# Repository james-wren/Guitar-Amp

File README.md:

# Guitar-Amp
## Description
A 4 inch and electric guitar amplifier using the LM386n-4 and J201 JFETS. Operates using 4 main stages:
1. JFET input boost, the signal coming from a guitar is very weak, so it needs to be boosted to a usable level
2. Tone control, uses a 50k POT to control the guitars tone, this stage decreases the signal strength
3. JFET tone boost, boosts the signal strength back up to usable level.
4. Audio amplification, uses the LM386n-4 to amplify the audio to ~1w, ideal for a 4 inch speaker

The board is designed to use only THT components to save money as it can ban easily soldered with basic tools, to aid in the easy assembly parts are also spread out over a almost 200mm width. Components start on the left with the 1/4 inch jack input, wrap around the top, and end on the right with the speaker output. It is mounted to the case using m2 screws.

The case is pretty simple, just a speaker on the front with the three potentiometers and input jack up top, the 12v barrel is located on the back of the case near the bottom, the case is printed in two parts, the back plate is printed seperatly and screwed on with two M2 screws.

Inside mounting holes of back plate:  

## Instructions
### Build 
1. Solder components onto the pcb, simply solder the through hole components, no special gear is needed.
2. Wire potentiometers, the input jack, 12v barrel, and the speaker. Solder using 22AWG wire to thier respective pads
3. Print case in any orientation prefered, note that supports will be needed for the main body.
4. Screw in components, the pcb and backplate use m2 screws, and the speaker uses m8.

### Usage
1. Plug in guitar, reccomend starting with this to avoid a loud, high piched noise.
2. Plug in 12v barrel to turn on amp
3. Adjust knobs to prefered tune
4. Play your guitar!

## Why I made this
Pretty simple, I don't have an AMP, but I do have a guitar (I actually built it myself). After building I decieded that I wanted to learn to play, until this I had been plugging it into my old ipod and using garage band as an amp, but this was pretty terrible so I decieded this would be a fun first hardware project

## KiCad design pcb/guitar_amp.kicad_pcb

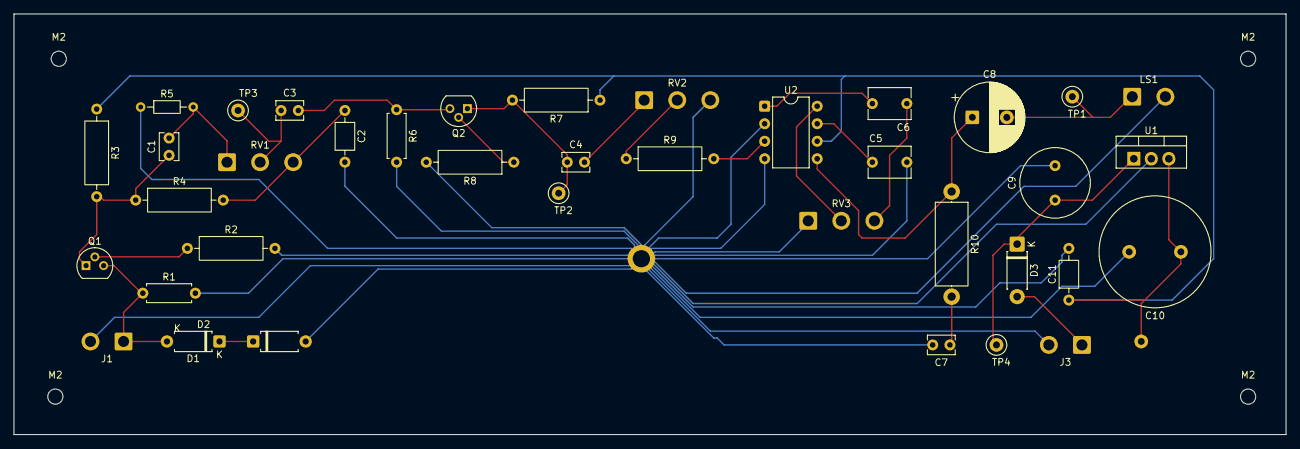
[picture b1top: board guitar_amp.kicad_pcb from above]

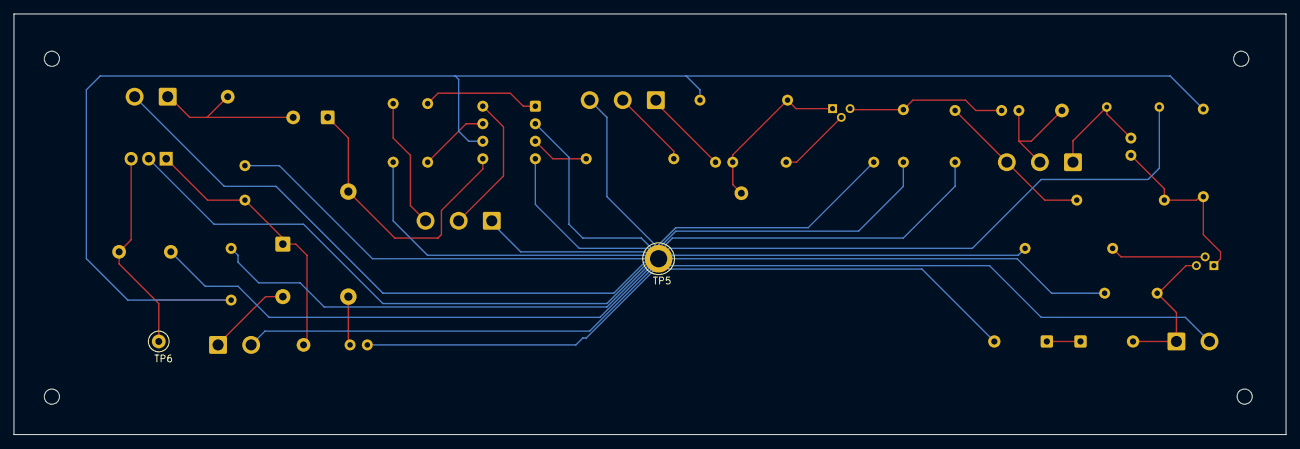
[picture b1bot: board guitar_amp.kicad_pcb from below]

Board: 2 copper layers, 184.5 x 61.0 mm, 44 parts (2 on the bottom side), 24 nets.

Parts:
C1: 6.8N; C_Disc_D3.8mm_W2.6mm_P2.50mm
C2: 10n; C_Axial_L3.8mm_D2.6mm_P7.50mm_Horizontal
C3, C4, C7: 47n; C_Disc_D3.8mm_W2.6mm_P2.50mm
C5, C6: 10uF; C_Disc_D6.0mm_W4.4mm_P5.00mm
C8: 220uF; CP_Radial_D10.0mm_P5.00mm
C9: 100uF; C_Radial_D10.0mm_H16.0mm_P5.00mm
C10: 470uF; C_Radial_D16.0mm_H31.5mm_P7.50mm
C11: 100nF; C_Axial_L3.8mm_D2.6mm_P7.50mm_Horizontal
D1, D2: 5.1v; D_A-405_P7.62mm_Horizontal
D3: 1N4007; D_DO-41_SOD81_P7.62mm_Horizontal
J1: 6.35mm Mono Jack; SolderWire-0.75sqmm_1x02_P4.8mm_D1.25mm_OD2.3mm
J3: Conn_Coaxial; SolderWire-0.75sqmm_1x02_P4.8mm_D1.25mm_OD2.3mm
LS1: 5 inch speaker; SolderWire-0.75sqmm_1x02_P4.8mm_D1.25mm_OD2.3mm
M2, M2#2, M2#3, M2#4: MountingHole_2.2mm_M2
Q1, Q2: J201; TO-92
R1, R6: 1M; R_Axial_DIN0207_L6.3mm_D2.5mm_P7.62mm_Horizontal
R2, R8: 2K2; R_Axial_DIN0309_L9.0mm_D3.2mm_P12.70mm_Horizontal
R3, R7, R9: 6K8; R_Axial_DIN0309_L9.0mm_D3.2mm_P12.70mm_Horizontal
R4: 47K; R_Axial_DIN0309_L9.0mm_D3.2mm_P12.70mm_Horizontal
R5: 22K; R_Axial_DIN0204_L3.6mm_D1.6mm_P7.62mm_Horizontal
R10: 10R; R_Axial_DIN0414_L11.9mm_D4.5mm_P15.24mm_Horizontal
RV1, RV3: 50K; SolderWire-0.75sqmm_1x03_P4.8mm_D1.25mm_OD2.3mm
RV2: A50K; SolderWire-0.75sqmm_1x03_P4.8mm_D1.25mm_OD2.3mm
TP1: Speaker; TestPoint_Loop_D2.50mm_Drill1.0mm
TP2: Boost; TestPoint_Loop_D2.50mm_Drill1.0mm
TP3: Tone; TestPoint_Loop_D2.50mm_Drill1.0mm
TP4: 12v Raw; TestPoint_Loop_D2.50mm_Drill1.0mm
TP5: GND Ref; TestPoint_Loop_D3.80mm_Drill2.5mm
TP6: 9v; TestPoint_Loop_D2.50mm_Drill1.0mm
U1: L7809; TO-220-3_Vertical
U2: LM386n-4; DIP-8_W7.62mm

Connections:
BOOST_OUT: C4.1, Q2.1 (D), R7.2, TP2.1 (1_1)
GND: C2.2, C5.2, C7.2, C9.2, C10.2, C11.2, D2.2 (A), J1.2, J3.2 (Ext), LS1.2, R1.2, R2.2, R5.1, R6.2, R8.2, RV2.3, RV3.1, TP5.1 (1_1), U1.2 (GND), U2.2 (-), U2.4 (GND)
INPUT_OUT: C1.1, Q1.1 (D), R3.2, R4.1
unnamed: C1.2, R5.2, RV1.1
unnamed: C2.1, R4.2, RV1.3
unnamed: C4.2, RV2.1
unnamed: C6.1, RV3.3
unnamed: C6.2, U2.1 (GAIN)
unnamed: C7.1, R10.2
unnamed: C8.1, R10.1, U2.5
unnamed: C8.2, LS1.1, TP1.1 (1_1)
unnamed: D1.2 (A), J1.1, Q1.3 (G), R1.1
unnamed: D1.1 (K), D2.1 (K)
unnamed: D3.2 (A), J3.1 (In)
unnamed: C9.1, D3.1 (K), TP4.1 (1_1), U1.1 (IN)
unnamed: Q1.2 (S), R2.1
unnamed: C3.2, Q2.3 (G), R6.1
unnamed: Q2.2 (S), R8.1
unnamed: R9.1, RV2.2
unnamed: RV3.2, U2.8 (GAIN)
unnamed: R9.2, U2.3 (+)
unnamed: C5.1, U2.7 (BYPASS)
TONE_OUT: C3.1, RV1.2, TP3.1 (1_1)
VCC: C10.1, C11.1, R3.1, R7.1, TP6.1 (1_1), U1.3 (OUT), U2.6 (V+)

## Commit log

2026-06-07 Create case dir
2026-06-07 Create pcb dir
2026-06-07 Added 3d files
2026-06-07 Added pcb files
2026-06-07 Added digikey BOM
2026-06-07 Rename Guitar amp.csv to digikey_bom.csv
